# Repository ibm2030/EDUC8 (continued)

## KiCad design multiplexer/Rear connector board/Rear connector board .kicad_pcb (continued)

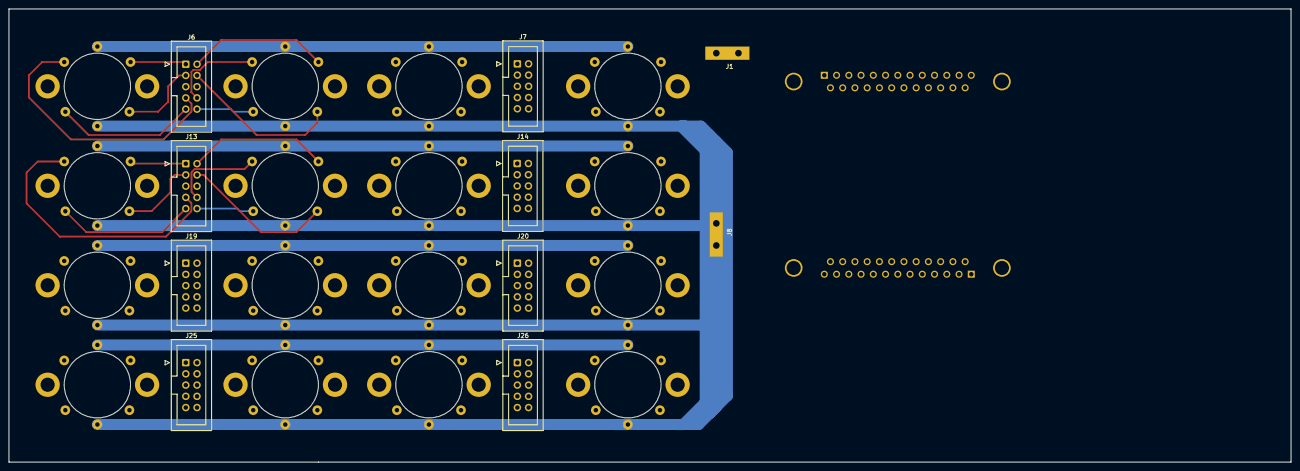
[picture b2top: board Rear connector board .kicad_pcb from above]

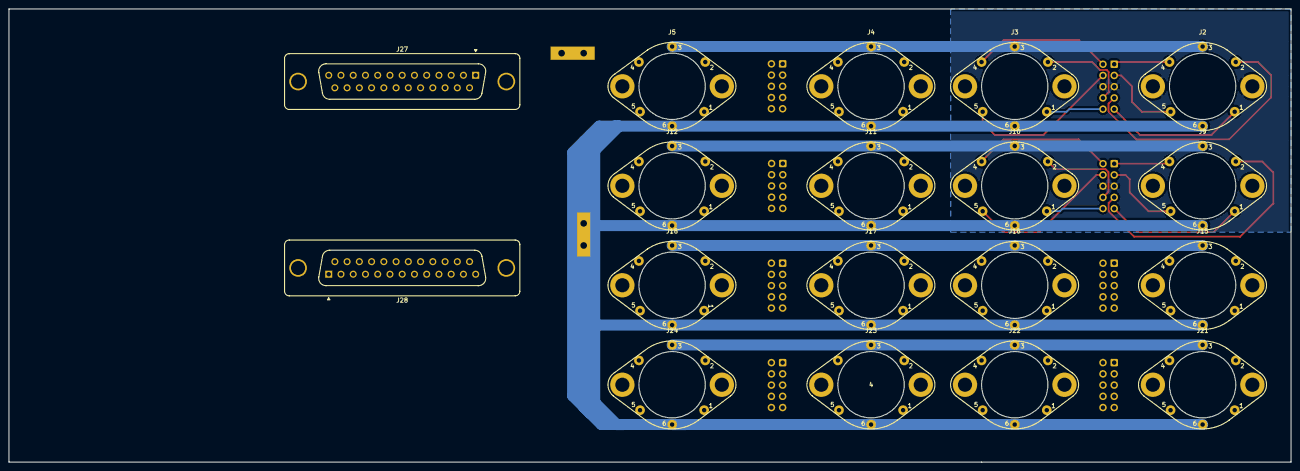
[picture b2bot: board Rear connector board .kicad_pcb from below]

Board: 2 copper layers, 290.0 x 102.5 mm, 28 parts (18 on the bottom side), 66 nets.

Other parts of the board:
J27: DB25_Female_MountingHoles; DSUB-25_Female_Vertical_P2.77x2.84mm_MountingHoles

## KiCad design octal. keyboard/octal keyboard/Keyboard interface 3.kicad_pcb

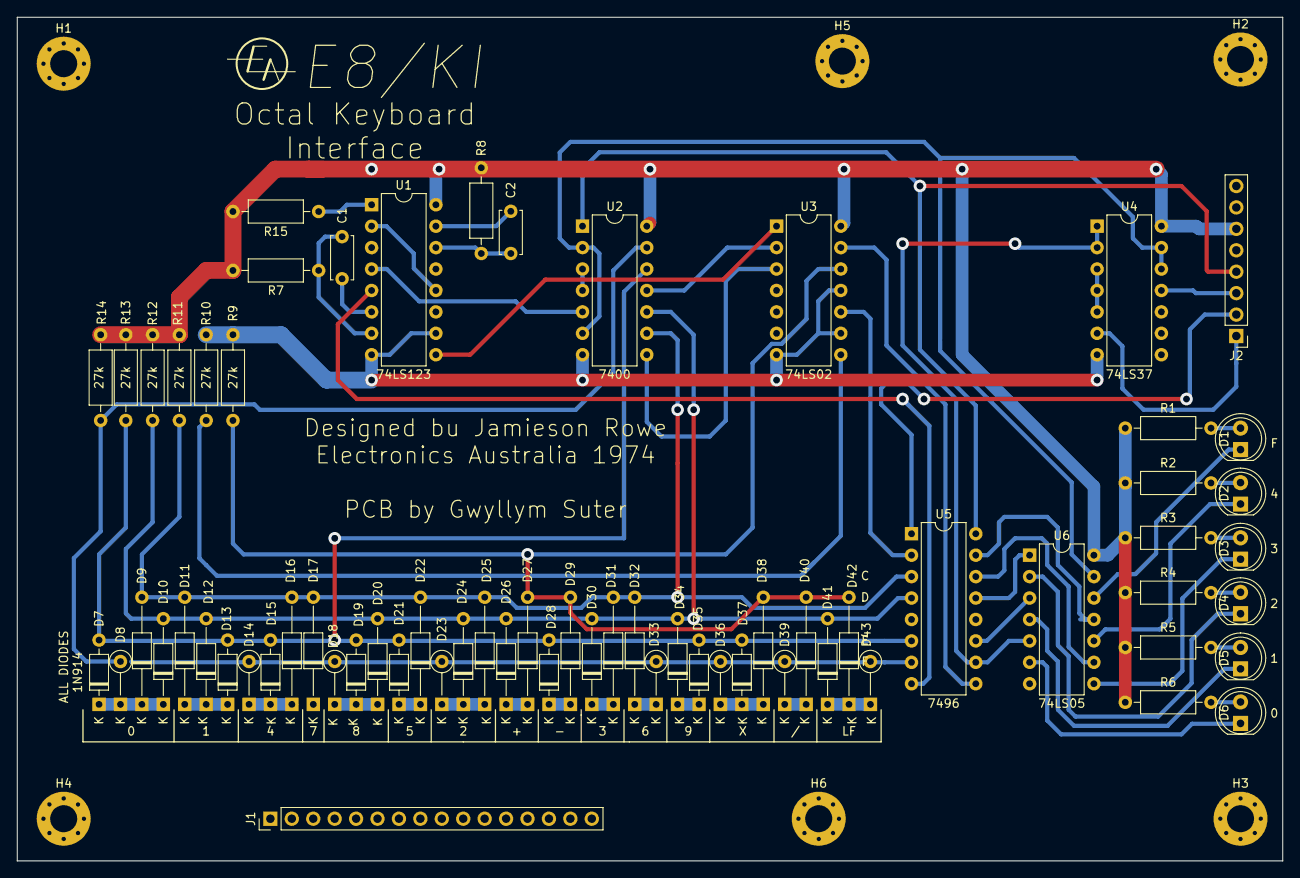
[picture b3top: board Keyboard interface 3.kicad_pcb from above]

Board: 2 copper layers, 150.0 x 100.0 mm, 74 parts (0 on the bottom side), 60 nets.

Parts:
C1: 1nF; C_Disc_D5.0mm_W2.5mm_P5.00mm
C2: 100pF; C_Disc_D5.0mm_W2.5mm_P5.00mm
D1, D2, D3, D4, D5, D6: LED; LED_D5.0mm
D7, D13, D15, D19, D21, D28, D35, D37: 1N914; D_DO-35_SOD27_P7.62mm_Horizontal
D8, D14, D18, D23, D33, D36, D39, D43: 1N914; D_DO-35_SOD27_P5.08mm_Vertical_KathodeUp
D9, D11, D16, D17, D22, D25, D27, D29, D31, D32, D38, D40, D42: 1N914; D_DO-35_SOD27_P12.70mm_Horizontal
D10, D12, D20, D24, D26, D30, D34, D41: 1N914; D_DO-35_SOD27_P10.16mm_Horizontal
H1, H2, H3, H4, H5, H6: MountingHole_Pad; MountingHole_3.2mm_M3_Pad_Via
J1: Conn_01x16_Male; PinHeader_1x16_P2.54mm_Vertical
J2: Conn_01x08_Male; PinHeader_1x08_P2.54mm_Vertical
R1, R2, R3, R4, R5, R6, R8: 180R; R_Axial_DIN0207_L6.3mm_D2.5mm_P10.16mm_Horizontal
R7: 33k; R_Axial_DIN0207_L6.3mm_D2.5mm_P10.16mm_Horizontal
R9, R10, R11, R12, R13, R14: 27k; R_Axial_DIN0207_L6.3mm_D2.5mm_P10.16mm_Horizontal
R15: 1k; R_Axial_DIN0207_L6.3mm_D2.5mm_P10.16mm_Horizontal
U1: 74LS123; DIP-16_W7.62mm
U2: 7400; DIP-14_W7.62mm
U3: 74LS02; DIP-14_W7.62mm
U4: 74LS37; DIP-14_W7.62mm
U5: 7496; DIP-16_W7.62mm
U6: 74LS05; DIP-14_W7.62mm

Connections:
0: D7.1, D8.1, D9.1, D10.1, J1.1
1: D11.1, D12.1, D13.1, J1.2
2: D23.1, D24.1, D25.1, J1.7
3: D30.1, D31.1, J1.10
4: D14.1, D15.1, D16.1, J1.3
5: D21.1, D22.1, J1.6
6: D32.1, D33.1, J1.11
7: D17.1, J1.4
8: D18.1, D19.1, D20.1, J1.5
9: D34.1, D35.1, J1.12
+: D26.1, D27.1, J1.8
+5V: J2.5, J2.6, R1.1, R2.1, R3.1, R4.1, R5.1, R6.1, R7.2, R8.2, R11.1, R12.1, R13.1, R14.1, R15.2, U1.16, U2.14, U3.14, U4.14, U6.14
-: D28.1, D29.1, J1.9
A: D27.2, D29.2, D38.2, D40.2, D42.2, R9.2, U3.12
C: D9.2, D11.2, D16.2, D17.2, D22.2, D25.2, D31.2, D32.2, R11.2, U2.9, U5.3
CR: J1.16, R10.2, U3.8
D: D10.2, D12.2, D20.2, D24.2, D26.2, D30.2, D34.2, D41.2, R12.2, U2.10, U5.4
DATA_OUT: J2.1, U4.6
DIV: D39.1, D40.1, J1.14
E: D7.2, D13.2, D15.2, D19.2, D21.2, D28.2, D35.2, D37.2, R13.2, U2.12, U5.6
F: D8.2, D14.2, D18.2, D23.2, D33.2, D36.2, D39.2, D43.2, R14.2, U2.13, U5.7
FLAG_OUT_LED: U2.2, U2.6, U4.12, U4.13, U6.13
GND: H1.1, H2.1, H3.1, H4.1, H5.1, H6.1, J2.7, J2.8, R9.1, R10.1, U1.8, U1.10, U2.7, U3.7, U3.9, U3.11, U4.7, U6.7
LF: D41.1, D42.1, D43.1, J1.15
unnamed: C1.1, R7.1, U1.7
unnamed: C1.2, U1.6
unnamed: C2.1, R8.1, U1.14
unnamed: C2.2, U1.15
unnamed: D1.1, U6.12
unnamed: D1.2, R1.2
unnamed: D2.1, U6.10
unnamed: D2.2, R2.2
unnamed: D3.1, U6.8
unnamed: D3.2, R3.2
unnamed: D4.1, U6.2
unnamed: D4.2, R4.2
unnamed: D5.1, U6.4
unnamed: D5.2, R5.2
unnamed: D6.1, U6.6
unnamed: D6.2, R6.2
unnamed: R15.1, U1.1
unnamed: U1.4, U2.5
unnamed: U1.5, U5.8
unnamed: U1.9, U3.1
unnamed: U1.2, U1.12
unnamed: U2.3, U2.4
unnamed: U2.8, U3.3
unnamed: U2.11, U3.2
unnamed: U3.10, U5.2
unnamed: U3.13, U5.9
unnamed: U4.1, U4.2, U5.10, U6.5
unnamed: U4.3, U4.4, U4.5
unnamed: U5.11, U6.3
unnamed: U5.13, U6.1
unnamed: U5.14, U6.9
unnamed: U5.15, U6.11
X: D36.1, D37.1, D38.1, J1.13
~FLAG_OUT: J2.3, U4.11
~FLAG_RESET: J2.4, U2.1, U5.16
~SHIFT_CLOCK: J2.2, U5.1

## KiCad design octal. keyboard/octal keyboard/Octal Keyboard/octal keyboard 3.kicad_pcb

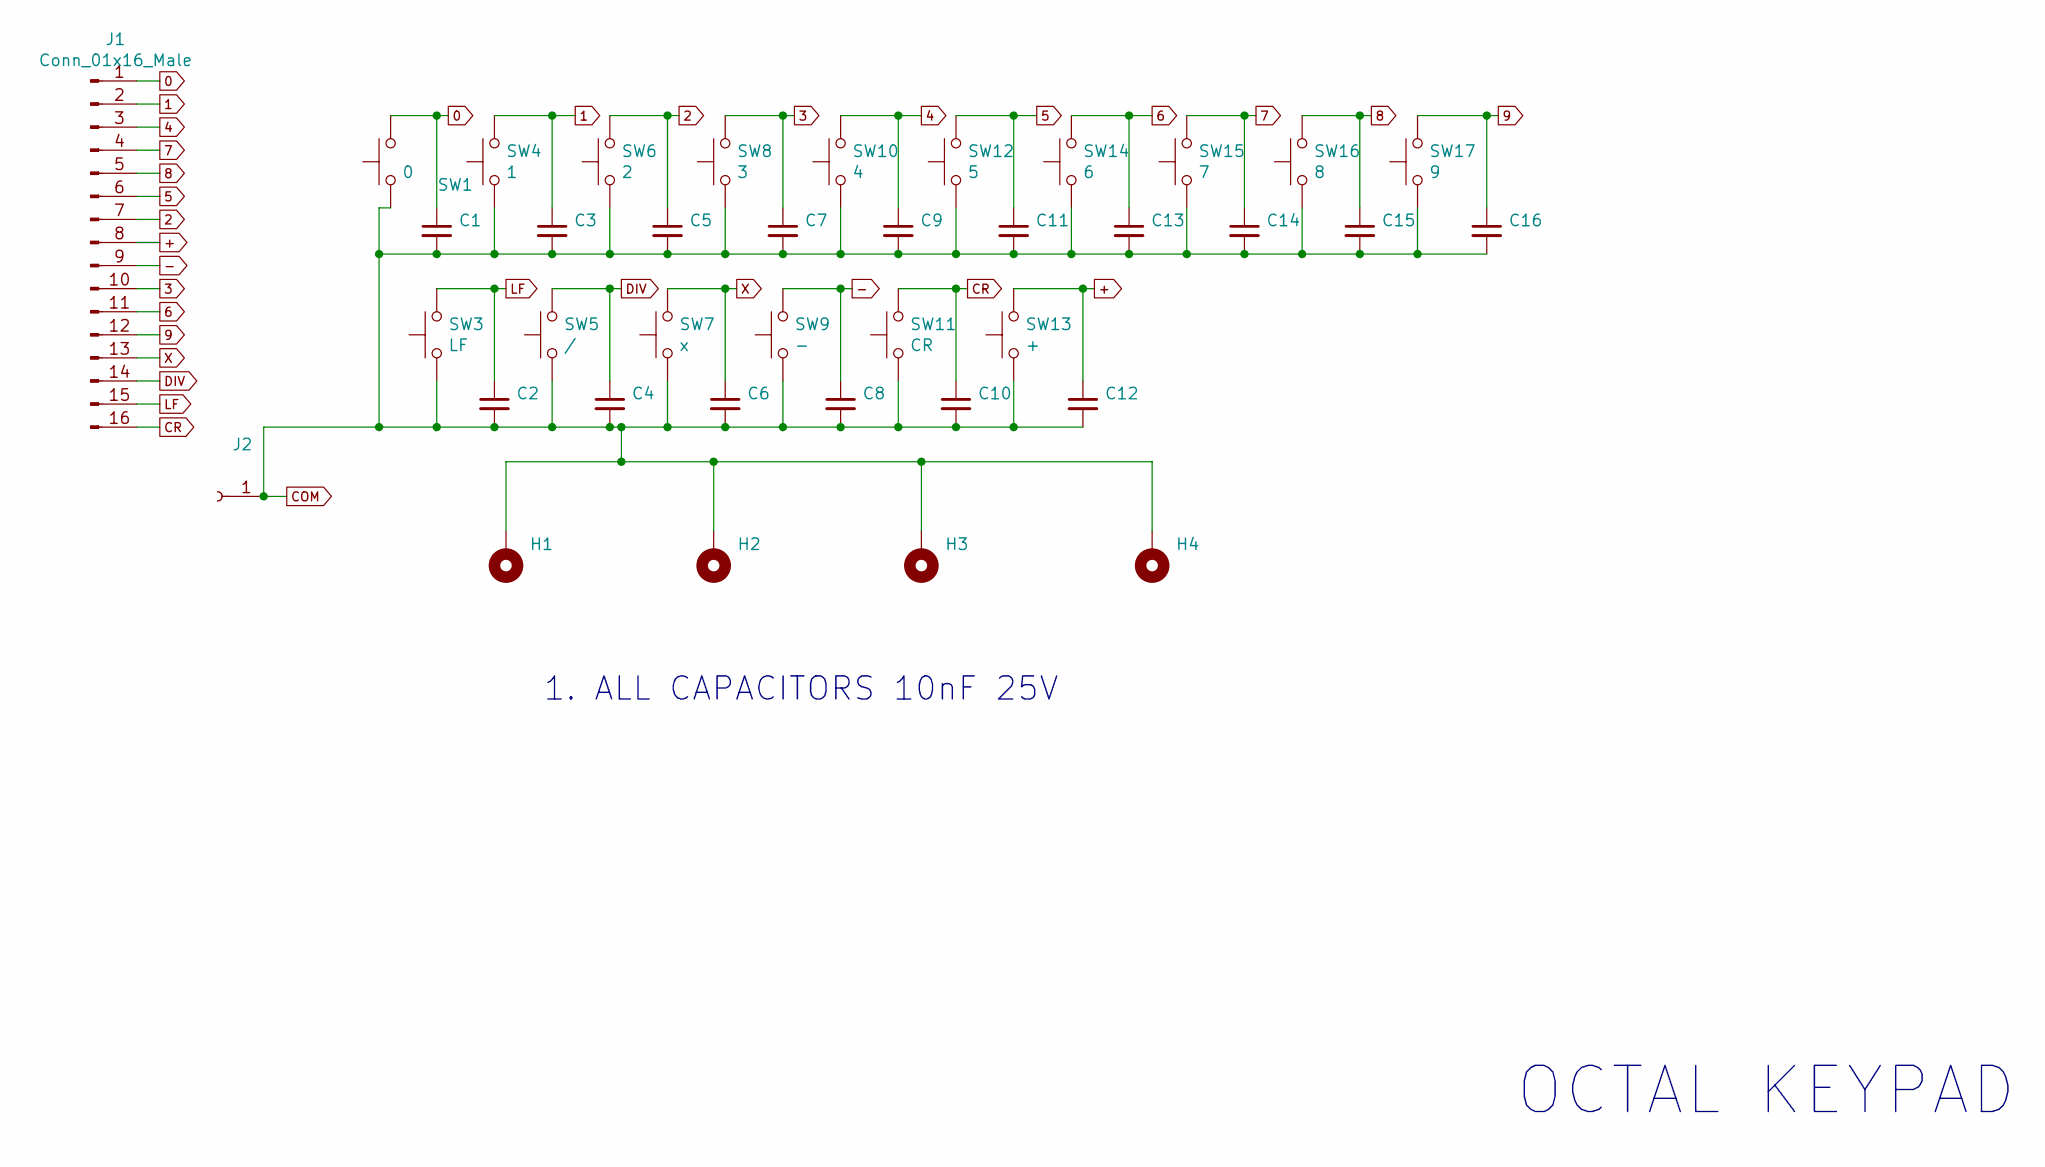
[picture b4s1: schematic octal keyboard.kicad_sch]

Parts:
C1, C3, C4, C5, C6, C7, C8, C9, C10, C11, C12, C13, C14, C15, C16: C_Small; C_Disc_D7.5mm_W2.5mm_P5.00mm
C2: 10nF; C_Disc_D7.5mm_W2.5mm_P5.00mm
H1, H2, H3, H4: MountingHole_Pad; MountingHole_3.2mm_M3_Pad_Via
J1: Conn_01x16_Male; PinHeader_1x16_P2.54mm_Vertical
J2: Conn_01x01_Female; PinHeader_1x01_P2.54mm_Vertical
SW1: 0; SW_Cherry_MX_1.00u_PCB
SW3: LF; SW_Cherry_MX_1.00u_PCB
SW4: 1; SW_Cherry_MX_1.00u_PCB
SW5: /; SW_Cherry_MX_1.00u_PCB
SW6: 2; SW_Cherry_MX_1.00u_PCB
SW7: x; SW_Cherry_MX_1.00u_PCB
SW8: 3; SW_Cherry_MX_1.00u_PCB
SW9: -; SW_Cherry_MX_1.00u_PCB
SW10: 4; SW_Cherry_MX_1.00u_PCB
SW11: CR; SW_Cherry_MX_1.00u_PCB
SW12: 5; SW_Cherry_MX_1.00u_PCB
SW13: +; SW_Cherry_MX_1.00u_PCB
SW14: 6; SW_Cherry_MX_1.00u_PCB
SW15: 7; SW_Cherry_MX_1.00u_PCB
SW16: 8; SW_Cherry_MX_1.00u_PCB
SW17: 9; SW_Cherry_MX_1.00u_PCB

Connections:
0: C1.1, J1.1, SW1.2
1: C3.1, J1.2, SW4.2
2: C5.1, J1.7, SW6.2
3: C7.1, J1.10, SW8.2
4: C9.1, J1.3, SW10.2
5: C11.1, J1.6, SW12.2
6: C13.1, J1.11, SW14.2
7: C14.1, J1.4, SW15.2
8: C15.1, J1.5, SW16.2
9: C16.1, J1.12, SW17.2
+: C12.1, J1.8, SW13.2
-: C8.1, J1.9, SW9.2
COM: C1.2, C2.2, C3.2, C4.2, C5.2, C6.2, C7.2, C8.2, C9.2, C10.2, C11.2, C12.2, C13.2, C14.2, C15.2, C16.2, H1.1, H2.1, H3.1, H4.1, J2.1, SW1.1, SW3.1, SW4.1, SW5.1, SW6.1, SW7.1, SW8.1, SW9.1, SW10.1, SW11.1, SW12.1, SW13.1, SW14.1, SW15.1, SW16.1, SW17.1
CR: C10.1, J1.16, SW11.2
DIV: C4.1, J1.14, SW5.2
LF: C2.1, J1.15, SW3.2
X: C6.1, J1.13, SW7.2

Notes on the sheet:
OCTAL KEYPAD
1. ALL CAPACITORS 10nF 25V

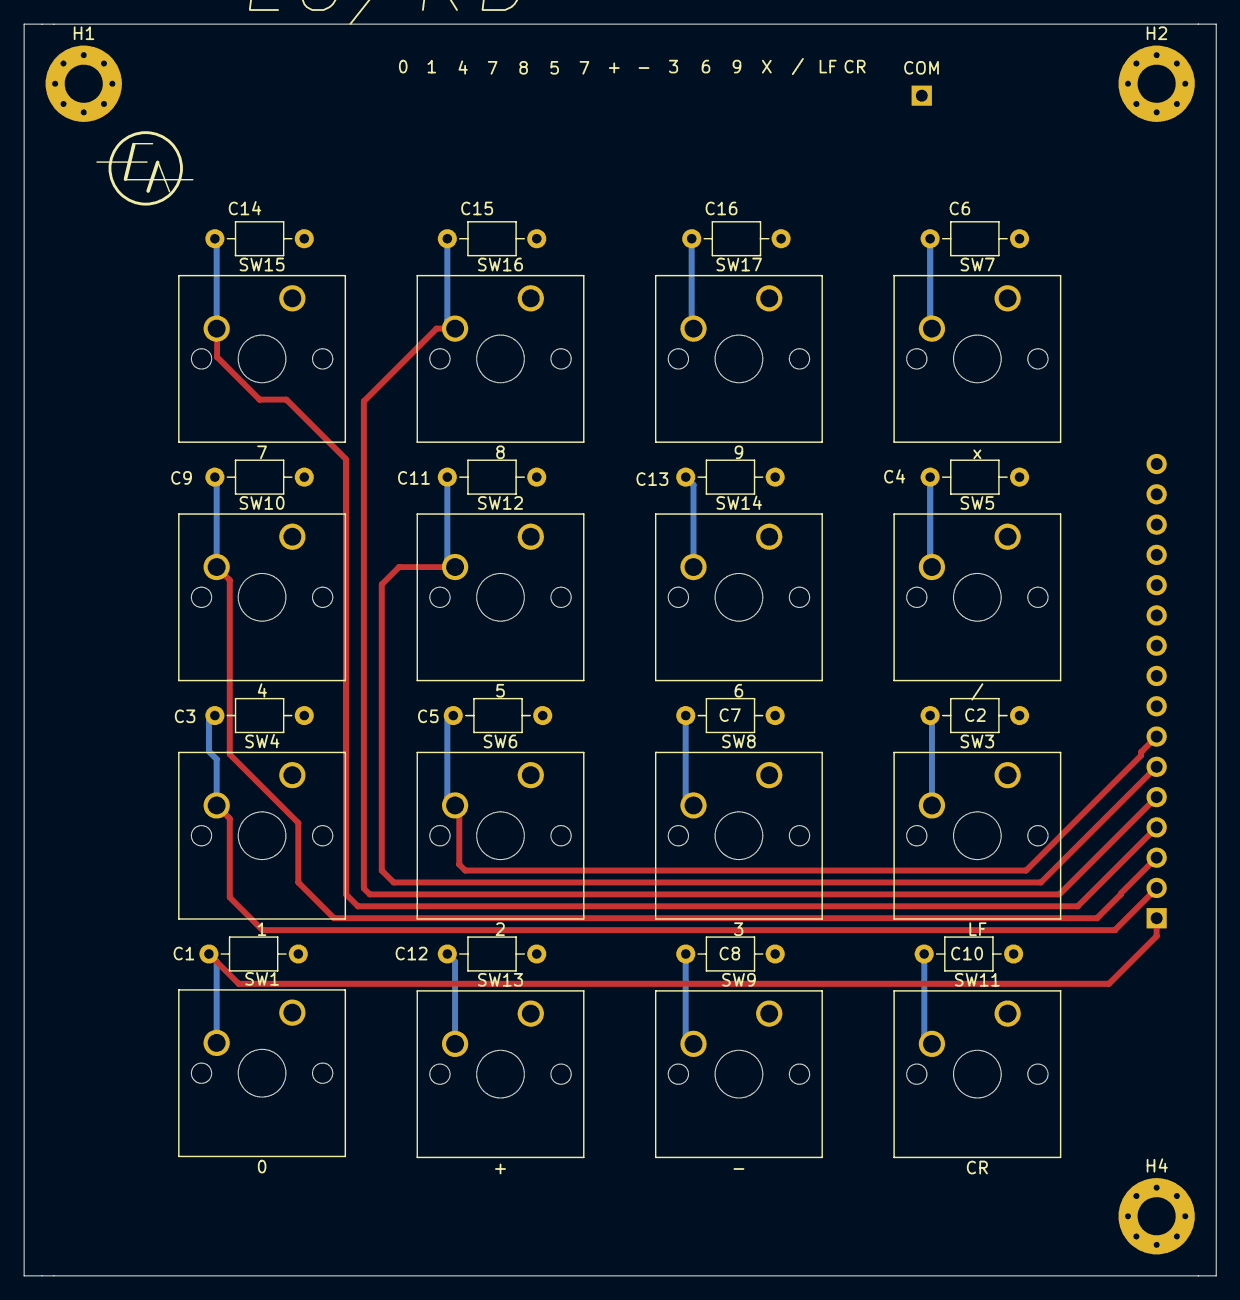
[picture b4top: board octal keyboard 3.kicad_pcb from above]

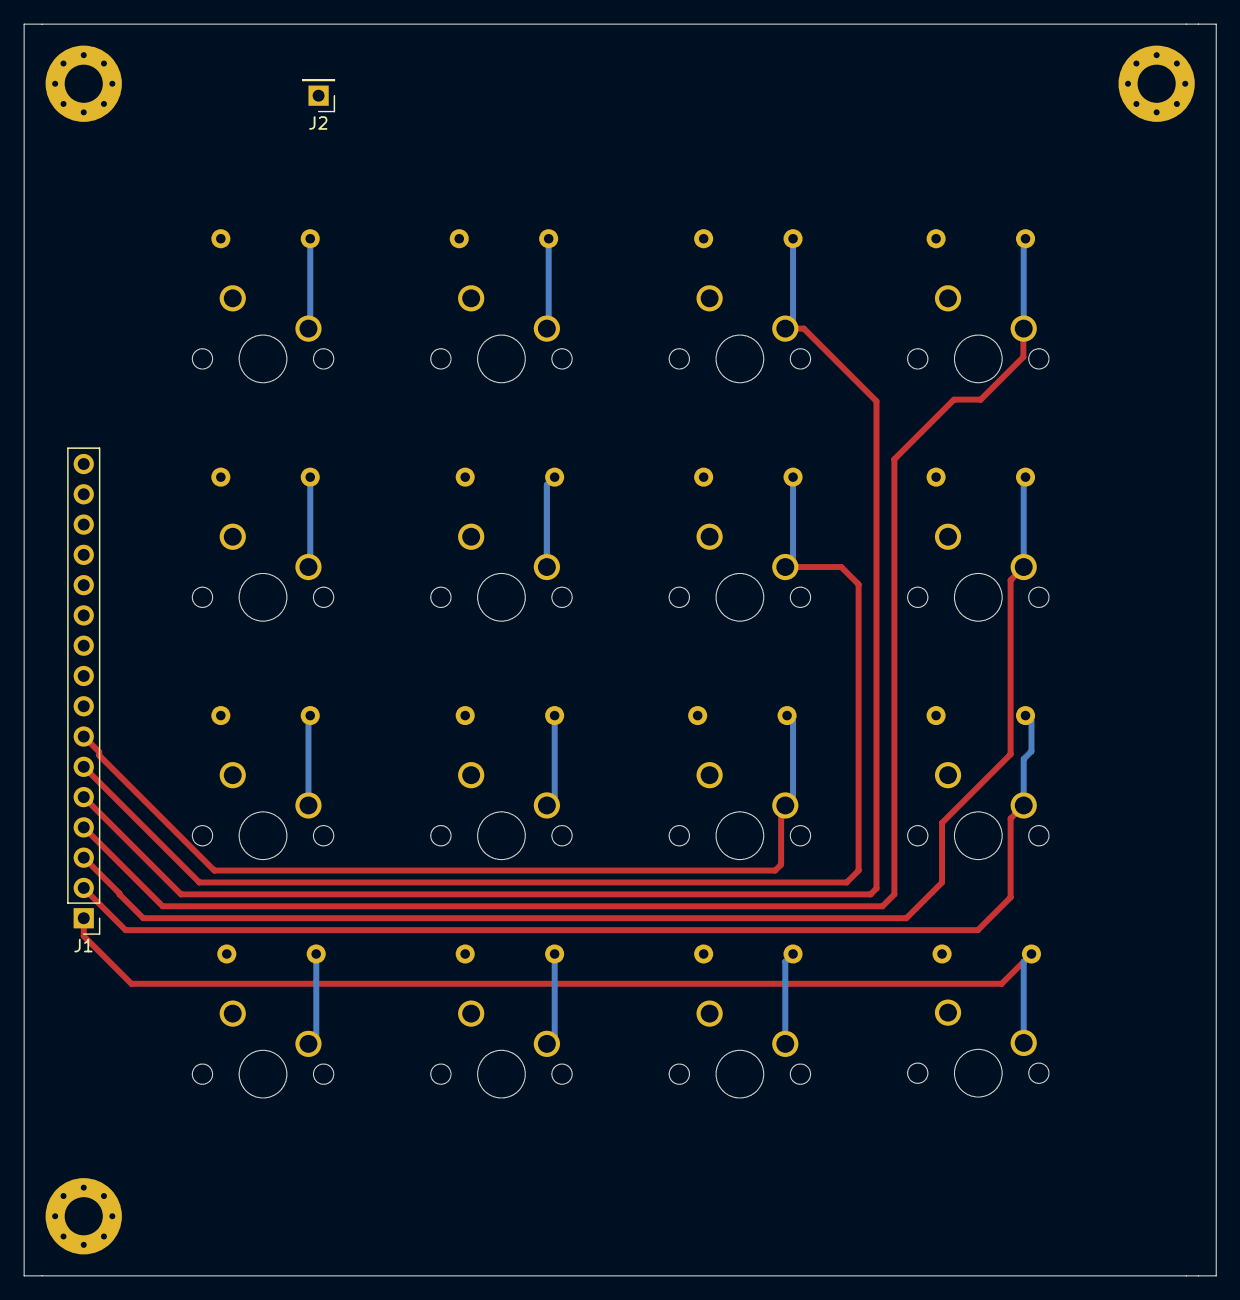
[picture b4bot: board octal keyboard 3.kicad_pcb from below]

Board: 2 copper layers, 100.0 x 105.0 mm, 37 parts (2 on the bottom side), 17 nets.

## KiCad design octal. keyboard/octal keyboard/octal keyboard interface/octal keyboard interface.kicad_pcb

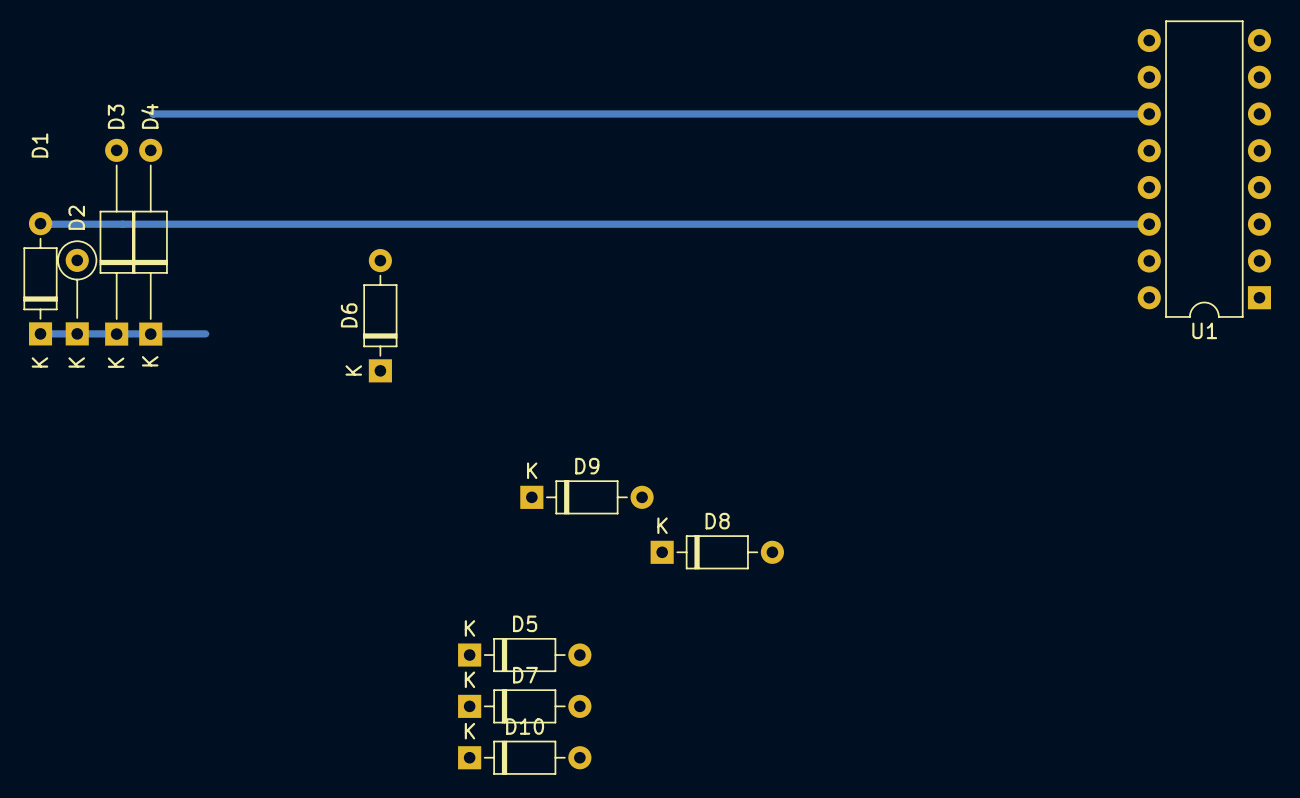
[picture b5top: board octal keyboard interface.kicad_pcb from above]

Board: 2 copper layers, 11 parts (0 on the bottom side), 8 nets.

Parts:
D1, D5, D6, D7, D8, D9, D10: 1N914; D_DO-35_SOD27_P7.62mm_Horizontal
D2: 1N914; D_DO-35_SOD27_P5.08mm_Vertical_KathodeUp
D3, D4: 1N914; D_DO-35_SOD27_P12.70mm_Horizontal
U1: 7496; DIP-16_W7.62mm

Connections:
0: D1.1, D2.1, D3.1, D4.1
1: D5.1, D6.1, D7.1
4: D8.1, D9.1, D10.1
K0: D2.2, U1.15
K1: D1.2, D7.2, U1.14
K2: D6.2, U1.13
K3: D4.2, D5.2, U1.11
K4: D3.2, U1.10
